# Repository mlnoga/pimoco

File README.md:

# pimoco

Telescope mount and focuser control with a Raspberry Pi 

## Motivation

Why do we need a separate device to control stepper motors attached to a telescope? Often times, a Raspberry Pi 4 running Ekos/Kstars/Indi will be attached to the telescope anyway, providing plenty of compute power. Modern stepper motor controllers like the Trinamic TMC5160 have an on-board motion controller which accepts position read, set target speed and go-to commands via SPI. The Raspberry Pi has two such interfaces for a total of five devices on its GPIO port.

This is 
* capable (1/256 microsteps, up to 1000x sidereal slewing, silent tracking, load-adaptive speed w/o step loss)
* robust (no Wifi, Bluetooth or USB connections to the mount as a source of error)
* beautiful (supports SkySafari on phones/tablets and game controllers via Ekos/Kstars/Indi) 
* inexpensive (no need for separate microcontrollers like OnStep or TeenAstro)
* manageable (no separate device firmware, only Indi drivers which Linux package managers can update)     

## [Wiki](../../wiki)

* [Hardware](../../wiki/Hardware)
* [Software](../../wiki/Software)
* [Results](../../wiki/Results)

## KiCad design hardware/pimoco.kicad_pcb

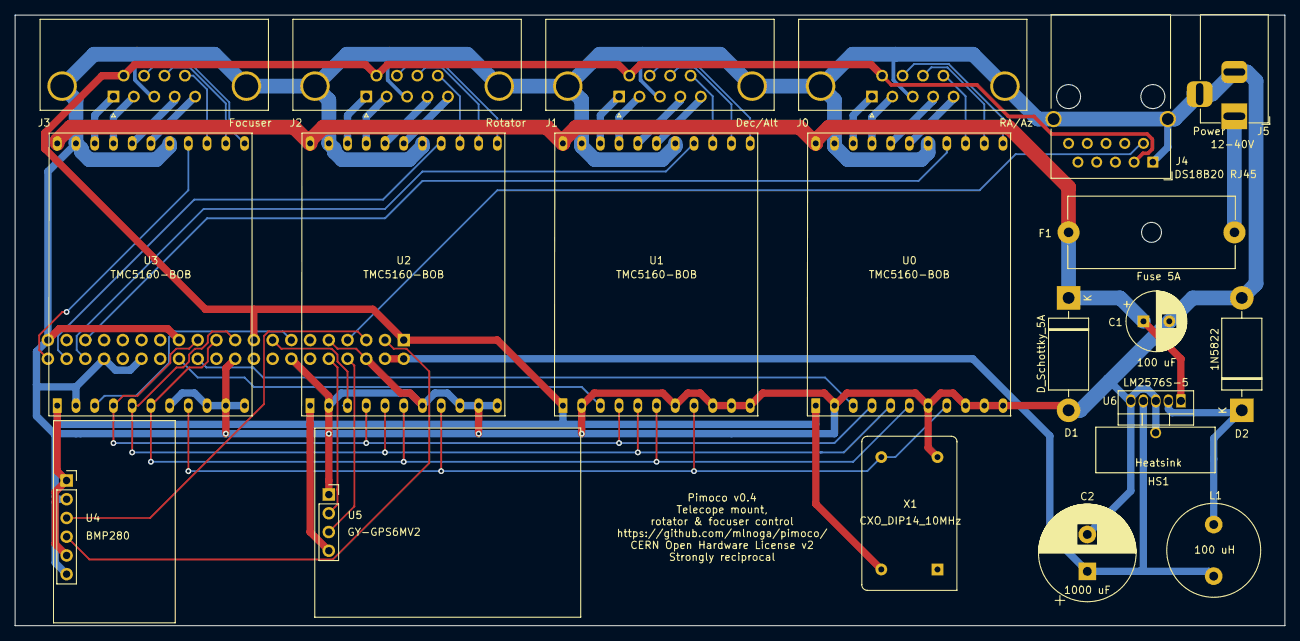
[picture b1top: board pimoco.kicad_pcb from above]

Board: 2 copper layers, 172.2 x 82.8 mm, 22 parts (1 on the bottom side), 51 nets.

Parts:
C1: 100 uF; CP_Radial_D8.0mm_P3.50mm
C2: 1000 uF; CP_Radial_D13.0mm_P5.00mm
D1: D_Schottky_5A; D_DO-201AD_P15.24mm_Horizontal
D2: 1N5822; D_DO-201AD_P15.24mm_Horizontal
F1: Fuse 5A; Fuseholder_Cylinder-5x20mm_Schurter_0031_8201_Horizontal_Op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
HS1: Heatsink; Heatsink_TO-220_vertical
J0: RA/Az; DSUB-9_Female_Horizontal_P2.77x2.84mm_EdgePinOffset7.70mm_H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
J1: Dec/Alt; DSUB-9_Female_Horizontal_P2.77x2.84mm_EdgePinOffset7.70mm_H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
J2: Rotator; DSUB-9_Female_Horizontal_P2.77x2.84mm_EdgePinOffset7.70mm_H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
J3: Focuser; DSUB-9_Female_Horizontal_P2.77x2.84mm_EdgePinOffset7.70mm_H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
J4: DS18B20 RJ45; RJ45_Wuerth_7499111446_Horizontal-modified
J5: Power; BarrelJack_Horizontal
J6: RasPi_Header; PinSocket_2x20_P2.54mm_Vertical
L1: 100 uH; L_Radial_D12.5mm_P7.00mm_Fastron_09HCP
U0, U1, U2, U3: TMC5160-BOB; TMC5160-BOB2
U4: BMP280; BMP280-Breakout
U5: GY-GPS6MV2
U6: LM2576S-5; TO-220-5_Vertical
X1: CXO_DIP14_10MHz; Oscillator_DIP-14

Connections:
+3V3: J0.6, J1.6, J2.6, J3.6, J4.3, J6.1, J6.17, U0.1, U1.1, U2.1, U3.1, U4.1, U4.5, U5.4, X1.14
+5V: C2.1, J6.2, J6.4, L1.2, U6.4
CE0: J6.24, U0.3
CE1: J6.26, U1.3
CE2: J6.15, U2.3
CE3: J6.13, U3.3
CLK: U0.8, U1.8, U2.8, U3.8, X1.8
DIAG0_0: J6.35, U0.19
DIAG0_1: J6.36, U1.19
DIAG0_2: J6.38, U2.19
DIAG0_3: J6.40, U3.19
GND: C1.2, C2.2, D1.2, D2.2, HS1.1, J0.0, J0.3, J1.0, J1.3, J2.0, J2.3, J3.0, J3.3, J4.1, J4.SH, J5.2, J5.3, J6.6, J6.9, J6.14, J6.20, J6.25, J6.30, J6.34, J6.39, U0.2, U0.7, U0.9, U0.10, U0.11, U0.13, U0.18, U1.2, U1.7, U1.9, U1.10, U1.11, U1.13, U1.18, U2.2, U2.7, U2.9, U2.10, U2.11, U2.13, U2.18, U3.2, U3.7, U3.9, U3.10, U3.11, U3.13, U3.18, U4.2, U4.6, U5.1, U6.3, U6.5, X1.7
MISO: J6.21, U0.6, U1.6, U2.6, U3.6
MOSI: J6.19, U0.5, U1.5, U2.5, U3.5
unnamed: D2.1, L1.1, U6.2
unnamed: F1.2, J5.1
unnamed: J0.1, U0.14
unnamed: J0.2, U0.15
unnamed: J0.4, U0.16
unnamed: J0.5, U0.17
unnamed: J0.7, U0.22
unnamed: J0.8, U0.21
unnamed: J0.9, U0.20
unnamed: J1.1, U1.14
unnamed: J1.2, U1.15
unnamed: J1.4, U1.16
unnamed: J1.5, U1.17
unnamed: J1.7, U1.22
unnamed: J1.8, U1.21
unnamed: J1.9, U1.20
unnamed: J2.1, U2.14
unnamed: J2.2, U2.15
unnamed: J2.4, U2.16
unnamed: J2.5, U2.17
unnamed: J2.7, U2.22
unnamed: J2.8, U2.21
unnamed: J2.9, U2.20
unnamed: J3.1, U3.14
unnamed: J3.2, U3.15
unnamed: J3.4, U3.16
unnamed: J3.5, U3.17
unnamed: J3.7, U3.22
unnamed: J3.8, U3.21
unnamed: J3.9, U3.20
unnamed: J4.2, J6.7
unnamed: J6.3, U4.4
unnamed: J6.5, U4.3
unnamed: J6.8, U5.3
unnamed: J6.10, U5.2
SCLK: J6.23, U0.4, U1.4, U2.4, U3.4
VCC: C1.1, D1.1, F1.1, U0.12, U1.12, U2.12, U3.12, U6.1

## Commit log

2021-03-22 Update README.md
    First repo setup with ideas and references
2021-03-22 Added first TMC5160 code. As yet uncompiled and untested
2021-03-23 compiles but doesn't communicate with device yet
2021-03-24 first version which communicates with Trinamic, doesn't yet move the motor
2021-03-24 implemented syncing of current position, caching of write-only register values in driver for convenience, and structured logging
2021-03-24 added count target to measure LOCs
2021-03-24 added default TZeroWait
2021-03-24 added timestamp class
2021-03-24 added curent calculations from/to mA, improved use of system timer for blocking GoTos.
2021-03-24 factored out SPI communication in base class
2021-03-24 factored out basic device register functions in separate class
2021-03-24 factored out higher functions into stepper subclass
2021-03-24 using refactored stepper class
2021-03-24 updated status flag handling with enum
2021-03-24 added min/max position limits
2021-03-28 Added hardware setup
2021-03-29 close #5: first working breadboard
2021-03-29 close #1: first working version of the driver which can initialize and execute gotos on each of the three motors
2021-03-29 improved motor settings and added first RA hour and sidereal rate calculations
2021-03-31 towards #2: first indi focuser driver which compiles, still need to sort out the connection
2021-03-31 close #6: using the Pi's GPCLK0 to generate the CLK16 signal for the TMCs
2021-03-31 updated build instructions in line with #2
2021-03-31 updated build instructions with libindi-dev dependency
2021-04-03 towards #2: first working device connection
2021-04-03 close #2: first working indi focuser driver
2021-04-03 added executable names to .gitignore
2021-04-04 towards #7: added hold/run current controls
2021-04-04 towards #7: added UI controls for ramp settings
2021-04-04 close #14: changed implementation of stop() to use goto(current_position)
2021-04-05 close #15: refactored to use INDI logger methods in stepper-related classes
2021-04-05 added pragma once to headers
2021-04-05 towards #3: first mount class which compiles, runs, and initializes steppers
2021-04-05 towards #3: factored out stepper Indi UI code into stepper cllass
2021-04-06 added libnova for mount calculations
2021-04-06 factored out reversal of axis direction into stepper class
2021-04-06 factored out reversal of axis direction into stepper class, added first RA calculations with libnova
2021-04-06 factored out reversal of axis direction into stepper class, added steps/rev and gear ratio properties and calculation of angular positions
2021-04-06 added override keyword to virtual methods
2021-04-06 added load/save of configuration
2021-04-06 added property for motor clock in hz
2021-04-06 towards #3: added sidereal rate tracking
2021-04-07 factored out GetFocuserStatus()
2021-04-07 towards #3: support for multiple and custom tracking rates
2021-04-07 towards #3: added sync in units
2021-04-07 fixed error handling for focuser Connect()
2021-04-07 towards #3: added sync capability, factored out getter for local sidereal time
2021-04-07 towards #3: added setTargetPositionInUnits()
2021-04-07 towards #3: added goto
2021-04-07 close #20: added park/unpark and related functions
2021-04-07 close #25: added Abort() method
2021-04-08 close #21: added mount slewing commands MoveNS, MoveWE and SetSlewRate
2021-04-08 close #27: added XML files for Indi driver installation
2021-04-08 close #16: loading config data after property creation, continuously saving config data on changes from UI
2021-04-09 #18: added wiringPi library for interrupt handling
2021-04-09 #18: added connections to diag0 interrupt pins
2021-04-09 To #18: added diag0 pin
2021-04-09 To #18: added diag0 pins
2021-04-09 To #18: passthrough of diag0 pins
2021-04-09 To #18: first interrupt support which catches and resets interrupts; no other actions yet
2021-04-19 added optional GPS
2021-04-19 first stripboard working with telescope. close #9, close #10
2021-04-24 #18: re-enabling previous tracking rate from ISR
2021-04-24 replaced RPi clock output with crystal oscillator due to Pi4 compatibility issue
2021-04-24 #18: simplified re-enablement of tracking
2021-04-24 #26: first steps towards guiding
2021-04-24 isr fix & logging improvement
2021-04-24 RasPi 4 WiringPi fix
2021-04-24 #18: direct move to tracking for zero distance gotos
2021-04-24 #26: guider interface flag and UI controls
2021-04-24 #26: repaired variable rate tracking to test guiding
2021-04-26 better defaults
2021-04-26 made getters/setters public for use in mount class
2021-04-26 close #26: guiding
2021-04-27 added guider rate and max pulse UI controls to guider tab
2021-04-27 made getTimeMillis() static
2021-04-27 #30: resume tracking after manual movement commands like MoveNS
2021-04-28 #17: added basic properties for stallguard, fast chopper moes
2021-04-28 fixed park handling, deactivating guider motion on slew/goto/park
2021-04-28 close #17: enhanced motor controll with DCStep, StallGuard etc.
2021-04-30 better default
2021-04-30 close #34: persisting park state over shutdowns
2021-05-02 moved guide commands into separate file
2021-05-02 factored out more mount capabilities into individual files
2021-05-02 #35: refactoring pimoco_mount.cpp into multiple files
2021-05-02 #23: first working mount limits for min/max altitude
2021-05-02 close #22: added pier side support
2021-05-03 #24: first meridian flip code
2021-05-04 replaced libnova calls with corresponding indi calls
2021-05-04 changed placeholder for sidereal time from NaN to negative value
2021-05-04 brought default park position in line with german eq mounts to HA -6h, Dec 90°
2021-05-04 #24: can trigger meridian flip by clicking pier side buttons, fixed HA limit defaults
2021-05-04 #24: fixes towards meridian flip
2021-05-05 moved materials into wiki
2021-05-05 fixed links
2021-05-05 moved images to wiki
2021-05-09 #24: goto to current coordinates now triggers meridian flip
2021-05-09 #23: better logging for mount limits
2021-05-09 #40: now converting RA from hours to degrees for coordinate transformation
2021-05-09 #40: now converting RA from hours to degrees for distance calculation
2021-05-13 clarified microsteps
2021-05-13 #32: switched to SPI mode 3 at 4.5 MHz
2021-05-14 added tester
2021-05-20 fixed end of transmision CS behavior
2021-05-20 added test to gitignore
2021-05-24 #32: added dtoverlay files for spi0-3cs and spi-4cs
2021-05-24 #32: new wirings for DIAG0 pins compatible with mode 3 on spi0-4cs
2021-05-24 #32: move to single SPI ioctl with array of transfers
2021-05-25 #32: added axis names for tracing
2021-05-25 #32: added axis names for tracing, better ISR init/destroy, diag0 push/pull
2021-05-25 #32: added axis names for tracing, better ISR init/destroy
2021-05-25 #32: added HA goto accuracy threshold to avoid endless chase conditions at low speed
2021-05-25 moved to physical pin numbers for interrupts
2021-05-25 setup now uses interrupts, to detect wiring errors
2021-05-25 added spitests
2021-05-27 updated .gitignore
2021-05-31 #11: added first 2-layer PCB
2021-06-03 close #42: added sync button for custom rate tracking
2021-06-08 #41: moved to physical side of pier reporting, fixed automatic meridian flip
2021-06-14 added missing return value
2021-06-14 close #41: fixed HA mount limits to deal with edge case close to meridian
2021-06-15 #38, #43: made device & horizon coordinates & time explicit properties and updated limit checks accordingly
2021-06-16 #43: added refraction calculation
2021-07-04 fixed make install dependencies
2021-07-04 close #11: added PCB image
2021-12-04 Close #48: added missing .lib file

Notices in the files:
hardware/pimoco.kicad_pcb:
CERN Open Hardware License v2
